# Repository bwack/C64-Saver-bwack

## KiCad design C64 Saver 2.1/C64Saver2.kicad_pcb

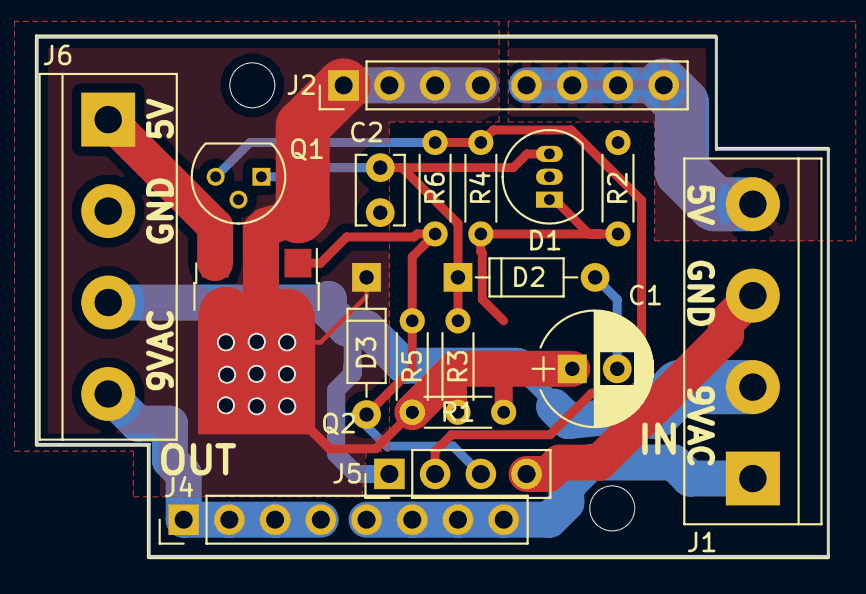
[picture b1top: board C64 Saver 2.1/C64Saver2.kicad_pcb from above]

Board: 2 copper layers, 43.9 x 28.8 mm, 20 parts (0 on the bottom side), 11 nets.

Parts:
C1: 47uF; CP_Radial_D6.3mm_P2.50mm
C2: 0.1uF; C_Disc_D3.8mm_W2.6mm_P2.50mm
D1: TL431LP; TO-92_Inline_Narrow_Oval
D2, D3: 6V8; D_DO-35_SOD27_P7.62mm_Horizontal
J1, J6: Conn_01x04; TerminalBlock_bornier-4_P5.08mm
J2, J4: Conn_01x08; Pin_Header_Straight_1x08_Pitch2.54mm
J5: Conn_01x04; Pin_Header_Straight_1x04_Pitch2.54mm
MK1, MK2: Mounting_Hole; MountingHole_2.5mm
Q1: 2N7002; TO-92_Molded_Narrow
Q2: Q_PMOS_GDS; ATPAK-2
R1, R2, R3, R4, R5, R6: R; R_Axial_DIN0204_L3.6mm_D1.6mm_P5.08mm_Horizontal

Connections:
/5V_SAFE: J6.1, Q2.3
/9VAC1: J1.1, J4.5, J4.6, J4.7, J4.8
/9VAC1': J4.1, J4.2, J4.3, J4.4, J6.4
/9VAC2: J1.2, J5.1, J6.3
/NGATE: C2.1, D1.3, D2.1, Q1.1, R3.2
/SENSE: D1.1, R1.2, R2.1, R4.1
/VCC1+: J1.4, J2.5, J2.6, J2.7, J2.8
/VCC1-: C1.1, D3.1, J2.1, J2.2, J2.3, J2.4, Q2.2, R1.1, R3.1, R5.1
GND: C1.2, C2.2, D1.2, D2.2, J1.3, J5.4, J6.2, Q1.2, R2.2
OVERVOLTAGE: J5.2, Q1.3, R4.2, R6.2
PGATE: D3.2, J5.3, Q2.1, R5.2, R6.1

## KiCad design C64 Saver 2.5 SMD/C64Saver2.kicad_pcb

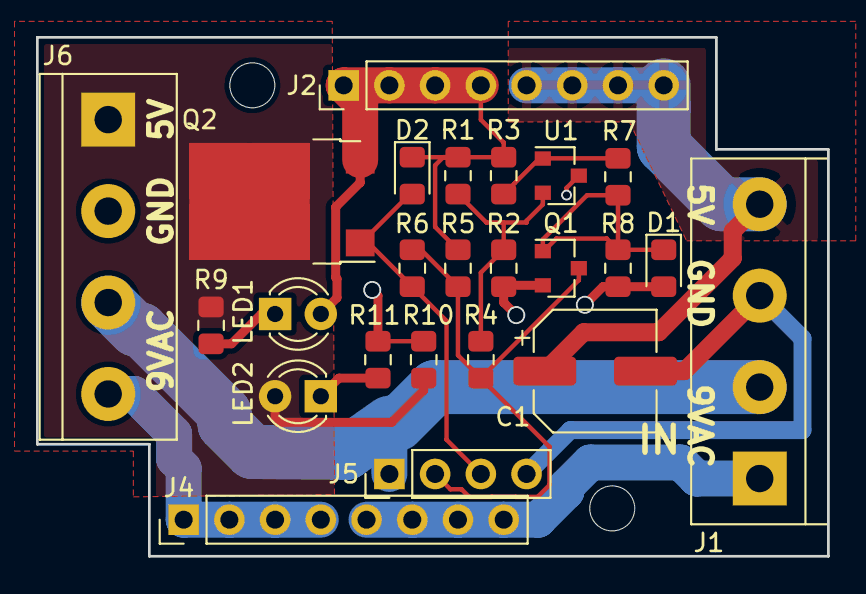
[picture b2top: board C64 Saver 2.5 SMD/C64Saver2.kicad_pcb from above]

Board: 2 copper layers, 43.9 x 28.8 mm, 26 parts (0 on the bottom side), 14 nets.

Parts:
C1: 47uF; CP_Elec_6.3x5.4
D1, D2: BZY55B6V8; D_0805_2012Metric_Pad1.15x1.40mm_HandSolder
J1, J6: Conn_01x04; TerminalBlock_bornier-4_P5.08mm
J2, J4: Conn_01x08; Pin_Header_Straight_1x08_Pitch2.54mm
J5: Conn_01x04; Pin_Header_Straight_1x04_Pitch2.54mm
LED1: LED_RED_3mm; LED_D3.0mm
LED2: LED_GREEN_3mm; LED_D3.0mm
MK1, MK2: Mounting_Hole; MountingHole_2.5mm
Q1: 2N7002; SOT-23
Q2: IRFR5305; ATPAK-2
R1, R6: 3k9; R_0805_2012Metric_Pad1.15x1.40mm_HandSolder
R2, R3, R5, R9, R10, R11: 3k3; R_0805_2012Metric_Pad1.15x1.40mm_HandSolder
R4: 330k; R_0805_2012Metric_Pad1.15x1.40mm_HandSolder
R7: 33k; R_0805_2012Metric_Pad1.15x1.40mm_HandSolder
R8: 82k; R_0805_2012Metric_Pad1.15x1.40mm_HandSolder
U1: TL431DBZ; SOT-23

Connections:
/5V_SAFE: J6.1, LED2.2, Q2.2, R9.1, R10.2
/9VAC1: J1.1, J4.5, J4.6, J4.7, J4.8
/9VAC1': J4.1, J4.2, J4.3, J4.4, J6.4
/9VAC2: J1.2, J5.1, J6.3
/NGATE: D1.1, Q1.1, R7.2, R8.1
/SENSE: R1.2, R2.1, R4.1, U1.2
/VCC1+: C1.1, J1.4, J2.5, J2.6, J2.7, J2.8
/VCC1-: D2.1, J2.1, J2.2, J2.3, J2.4, LED1.2, Q2.3, R1.1, R3.1, R5.1
GND: C1.2, D1.2, J1.3, J5.4, J6.2, Q1.2, R2.2, R8.2, R10.1, R11.1, U1.3
unnamed: LED1.1, R9.2
unnamed: LED2.1, R11.2
unnamed: R3.2, R7.1, U1.1
OVERVOLTAGE: J5.2, Q1.3, R4.2, R5.2, R6.2
PGATE: D2.2, J5.3, Q2.1, R6.1

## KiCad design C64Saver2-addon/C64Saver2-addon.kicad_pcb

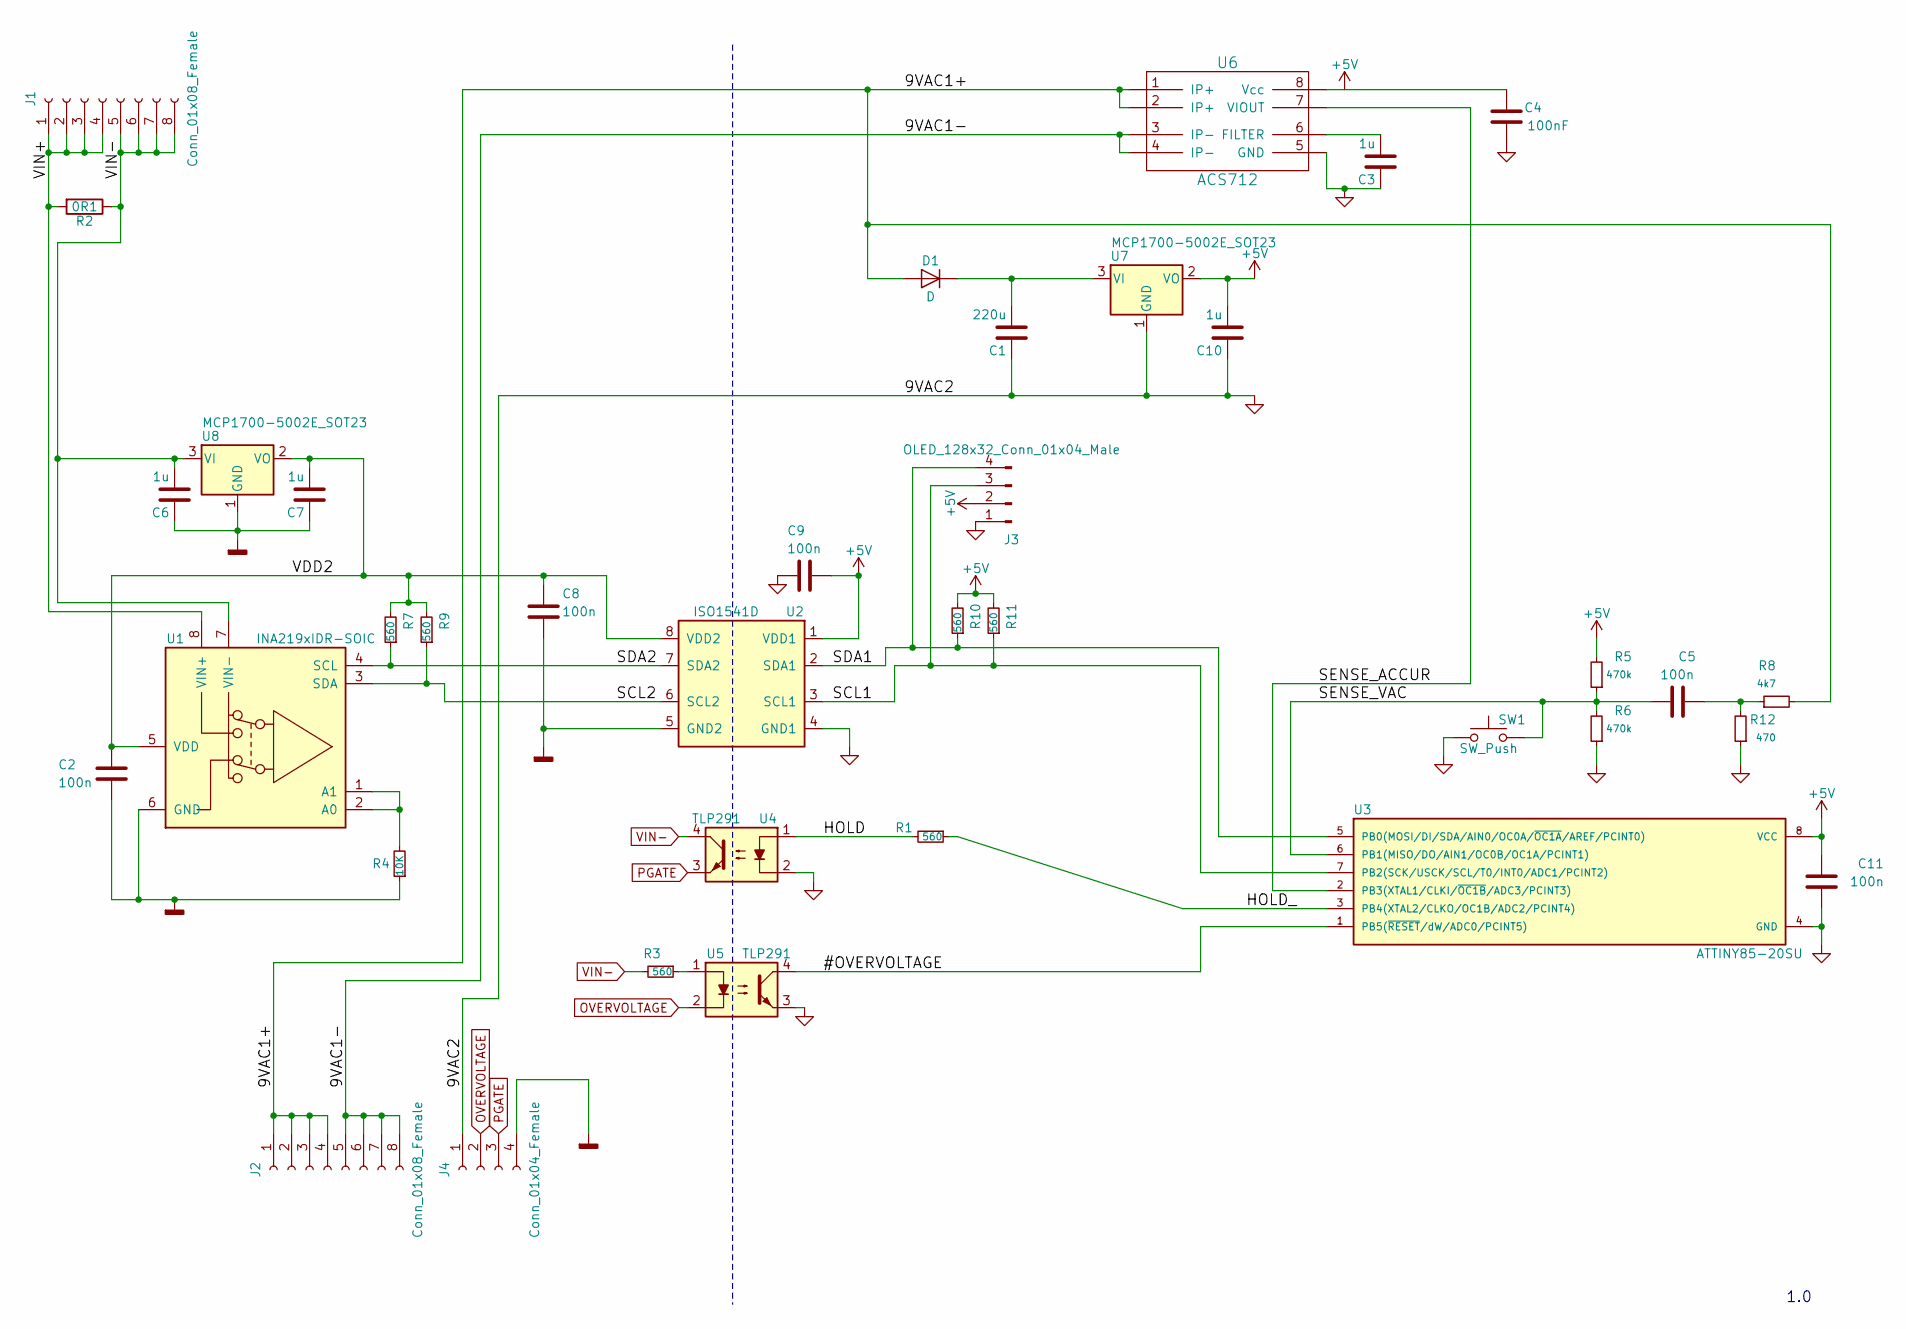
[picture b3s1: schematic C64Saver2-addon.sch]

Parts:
C1: 220u; C_1210_HandSoldering
C2, C5, C8, C9, C11: 100n; C_0603_HandSoldering
C3, C6, C7, C10: 1u; C_0603_HandSoldering
C4: 100nF; C_0603_HandSoldering
D1: D; D_SOD-123
J1, J2: Conn_01x08_Female; Pin_Header_Straight_1x08_Pitch2.54mm
J3: OLED_128x32_Conn_01x04_Male; Pin_Header_Straight_1x04_Pitch2.54mm
J4: Conn_01x04_Female; Pin_Header_Straight_1x04_Pitch2.54mm
R1, R3, R7, R9, R10, R11: 560; R_0603_HandSoldering
R2: 0R1; R_2010_HandSoldering
R4: 10K; R_0603_HandSoldering
R5, R6: 470k; R_0603_HandSoldering
R8: 4k7; R_0603_HandSoldering
R12: 470; R_0603_HandSoldering
SW1: SW_Push; SW_PUSH_6mm_h13mm
U1: INA219xIDR-SOIC; SOIC-8-N
U2: ISO1541D; SOIC-8-N
U3: ATTINY85-20SU; SOIC-8_3.9x4.9mm_Pitch1.27mm
U4, U5: TLP291; SO-4_7.6x3.6mm_Pitch2.54mm
U6: ACS712; SOIC-8-N
U7, U8: MCP1700-5002E_SOT23; SOT-23

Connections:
+5V: C4.2, C9.1, C10.2, C11.2, J3.2, R5.2, R10.2, R11.2, U2.1 (VDD1), U3.8 (VCC), U6.8 (Vcc), U7.2 (VO); also elsewhere on the board
/9VAC1+: D1.2 (A), J2.1, J2.2, J2.3, J2.4, R8.2, U6.1 (IP+), U6.2 (IP+)
/9VAC1-: J2.5, J2.6, J2.7, J2.8, U6.3 (IP-), U6.4 (IP-)
/#OVERVOLTAGE: U3.1 (PB5(~RESET~/dW/ADC0/PCINT5)), U5.4; also elsewhere on the board
/FILTER: C3.2, U6.6 (FILTER)
/HOLD: R1.2, U4.1
/HOLD_: R1.1, U3.3 (PB4(XTAL2/CLKO/OC1B/ADC2/PCINT4))
/SCL1: J3.3, R11.1, U2.3 (SCL1), U3.7 (PB2(SCK/USCK/SCL/T0/INT0/ADC1/PCINT2)); also elsewhere on the board
/SCL2: R9.1, U1.3 (SDA), U2.6 (SCL2)
/SDA1: J3.4, R10.1, U2.2 (SDA1), U3.5 (PB0(MOSI/DI/SDA/AIN0/OC0A/~OC1A~/AREF/P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); also elsewhere on the board
/SDA2: R7.1, U1.4 (SCL), U2.7 (SDA2)
/SENSE_ACCUR: U3.2 (PB3(XTAL1/CLKI/~OC1B~/ADC3/PCINT3)), U6.7 (VIOUT)
/SENSE_VAC: C5.2, R5.1, R6.2, SW1.2, U3.6 (PB1(MISO/DO/AIN1/OC0B/OC1A/PCINT1)); also elsewhere on the board
/VDD2: C2.1, C7.2, C8.1, R7.2, R9.2, U1.5 (VDD), U2.8 (VDD2), U8.2 (VO)
/VIN+: J1.1, J1.2, J1.3, J1.4, R2.2, U1.8 (VIN+)
GND: C1.1, C3.1, C4.1, C9.2, C10.1, C11.1, J3.1, J4.1, R6.1, R12.1, SW1.1, U2.4 (GND1), U3.4 (GND), U4.2, U5.3, U6.5 (GND), U7.1 (GND); also elsewhere on the board
GNDD: C2.2, C6.1, C7.1, C8.2, J4.4, R4.1, U1.6 (GND), U2.5 (GND2), U8.1 (GND)
unnamed: C1.2, D1.1 (K), U7.3 (VI)
unnamed: C5.1, R8.1, R12.2
unnamed: R3.1, U5.1
unnamed: R4.2, U1.1 (A1), U1.2 (A0)
OVERVOLTAGE: J4.2, U5.2
PGATE: J4.3, U4.3
VIN-: C6.2, J1.5, J1.6, J1.7, J1.8, R2.1, R3.2, U1.7 (VIN-), U4.4, U8.3 (VI)

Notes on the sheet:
1.0

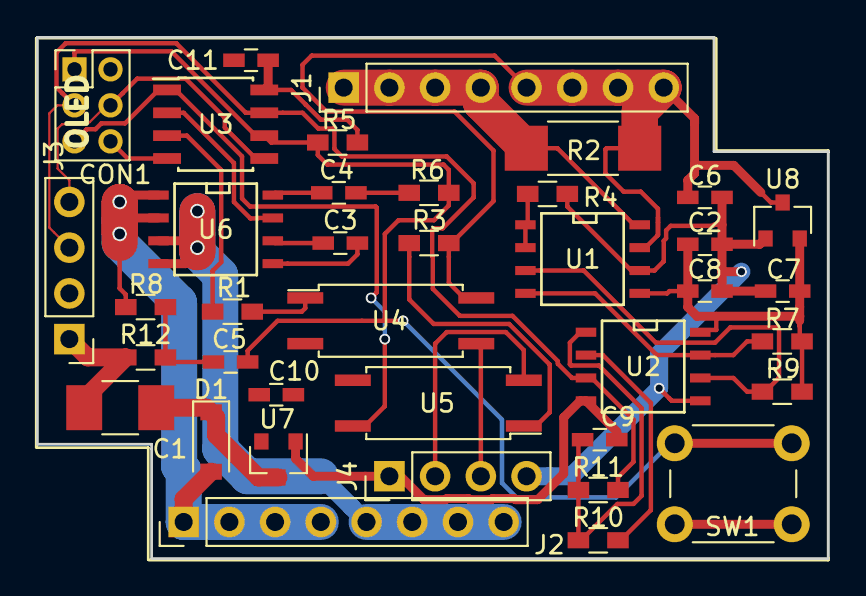
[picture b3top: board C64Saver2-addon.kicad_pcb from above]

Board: 2 copper layers, 43.9 x 29.0 mm, 38 parts (0 on the bottom side), 24 nets.

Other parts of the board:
CON1: AVR-ISP-6; Pin_Header_Straight_2x03_Pitch2.00mm

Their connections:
+5V: CON1.2; also elsewhere on the board
/#OVERVOLTAGE: CON1.5; also elsewhere on the board
/SCL1: CON1.3; also elsewhere on the board
/SDA1: CON1.4; also elsewhere on the board
/SENSE_VAC: CON1.1; also elsewhere on the board
GND: CON1.6; also elsewhere on the board

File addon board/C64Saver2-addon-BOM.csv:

"Source:","D:\Documents\GitHub\C64-Saver-bwack\addon board\C64Saver2-addon.sch"
"Date:","24.05.2019 00:26:36"
"Tool:","Eeschema (5.1.0)-1"
"Generator:","C:\Program Files\KiCad\bin\scripting\plugins/bom_csv_grouped_by_value.py"
"Component Count:","42"

"Individual Components:"

"Item","Qty","Reference(s)","Value","LibPart","Footprint","Datasheet"
"","","C1","47uF","Device:C_Small","Capacitor_SMD:C_1206_3216Metric","~"
"","","C2","100n","Device:C","Capacitors_SMD:C_0603_HandSoldering",""
"","","C3","1u","Device:C","Capacitors_SMD:C_0603_HandSoldering",""
"","","C4","100nF","Device:C","Capacitors_SMD:C_0603_HandSoldering",""
"","","C5","100n","Device:C","Capacitors_SMD:C_0603_HandSoldering",""
"","","C6","1u","Device:C","Capacitors_SMD:C_0603_HandSoldering",""
"","","C7","1u","Device:C","Capacitors_SMD:C_0603_HandSoldering",""
"","","C8","100n","Device:C","Capacitors_SMD:C_0603_HandSoldering",""
"","","C9","100n","Device:C","Capacitors_SMD:C_0603_HandSoldering",""
"","","C10","1u","Device:C","Capacitors_SMD:C_0603_HandSoldering",""
"","","C11","100n","Device:C","Capacitors_SMD:C_0603_HandSoldering",""
"","","C12","47uF","Device:C_Small","Capacitor_SMD:C_1206_3216Metric","~"
"","","C13","47uF","Device:C_Small","Capacitor_SMD:C_1206_3216Metric","~"
"","","CON1","AVR-ISP-6","C64Saver2-addon-rescue:AVR-ISP-6","Pin_Headers:Pin_Header_Straight_2x03_Pitch2.00mm",""
"","","D1","Dotec SL1G","Device:D","Diodes_SMD:D_SOD-123",""
"","","J1","Conn_01x08_Female","C64Saver2-addon-rescue:Conn_01x08_Female","Pin_Headers:Pin_Header_Straight_1x08_Pitch2.54mm",""
"","","J2","Conn_01x08_Female","C64Saver2-addon-rescue:Conn_01x08_Female","Pin_Headers:Pin_Header_Straight_1x08_Pitch2.54mm",""
"","","J3","OLED_128x32_Conn_01x04_Male","C64Saver2-addon-rescue:Conn_01x04_Male","Pin_Headers:Pin_Header_Straight_1x04_Pitch2.54mm",""
"","","J4","Conn_01x04_Female","C64Saver2-addon-rescue:Conn_01x04_Female","Pin_Headers:Pin_Header_Straight_1x04_Pitch2.54mm",""
"","","R1","560","Device:R_Small","Resistors_SMD:R_0603_HandSoldering",""
"","","R2","0R1","Device:R","Resistors_SMD:R_2512_HandSoldering",""
"","","R3","560","Device:R_Small","Resistors_SMD:R_0603_HandSoldering",""
"","","R4","10K","Device:R_Small","Resistors_SMD:R_0603_HandSoldering",""
"","","R5","470k","Device:R_Small","Resistors_SMD:R_0603_HandSoldering",""
"","","R6","470k","Device:R_Small","Resistors_SMD:R_0603_HandSoldering",""
"","","R7","4k7","Device:R_Small","Resistors_SMD:R_0603_HandSoldering",""
"","","R8","4k7","Device:R_Small","Resistors_SMD:R_0603_HandSoldering",""
"","","R9","4k7","Device:R_Small","Resistors_SMD:R_0603_HandSoldering",""
"","","R10","4k7","Device:R_Small","Resistors_SMD:R_0603_HandSoldering",""
"","","R11","4k7","Device:R_Small","Resistors_SMD:R_0603_HandSoldering",""
"","","R12","470","Device:R_Small","Resistors_SMD:R_0603_HandSoldering",""
"","","R13","10k","Device:R_Small","Resistors_SMD:R_0603_HandSoldering",""
"","","R14","1k","Device:R_Small","Resistors_SMD:R_0603_HandSoldering",""
"","","SW1","SW_Push","C64Saver2-addon-rescue:SW_Push","Buttons_Switches_THT:SW_PUSH_6mm_h13mm",""
"","","U1","INA219xIDR-SOIC","ina219:INA219xIDR-SOIC","SMD_Packages:SOIC-8-N",""
"","","U2","ISO1541D","iso1541d:ISO1541D","SMD_Packages:SOIC-8-N",""
"","","U3","ATTINY85-20SU","C64Saver2-addon-rescue:ATTINY85-20SU","Housings_SOIC:SOIJ-8_5.3x5.3mm_Pitch1.27mm",""
"","","U4","ACPL-217-50DE","C64Saver2-addon-rescue:TLP291","Package_SO:SOIC-4_4.55x2.6mm_P1.27mm",""
"","","U5","ACPL-217-50DE","C64Saver2-addon-rescue:TLP291","Package_SO:SOIC-4_4.55x2.6mm_P1.27mm",""
"","","U6","ACS712","acs712:ACS712","SMD_Packages:SOIC-8-N",""
"","","U7","MCP1703","C64Saver2-addon-rescue:MCP1700-5002E_SOT23","Package_TO_SOT_SMD:SOT-223-3_TabPin2",""
"","","U8","MCP1703","C64Saver2-addon-rescue:MCP1700-5002E_SOT23","TO_SOT_Packages_SMD:SOT-23",""



"Collated Components:"

"Item","Qty","Reference(s)","Value","LibPart","Footprint","Datasheet"
"1","3","C1, C12, C13","47uF","Device:C_Small","Capacitor_SMD:C_1206_3216Metric","~"
"2","5","C2, C5, C8, C9, C11","100n","Device:C","Capacitors_SMD:C_0603_HandSoldering",""
"3","4","C3, C6, C7, C10","1u","Device:C","Capacitors_SMD:C_0603_HandSoldering",""
"4","1","C4","100nF","Device:C","Capacitors_SMD:C_0603_HandSoldering",""
"5","1","CON1","AVR-ISP-6","C64Saver2-addon-rescue:AVR-ISP-6","Pin_Headers:Pin_Header_Straight_2x03_Pitch2.00mm",""
"6","1","D1","Dotec SL1G","Device:D","Diodes_SMD:D_SOD-123",""
"7","2","J1, J2","Conn_01x08_Female","C64Saver2-addon-rescue:Conn_01x08_Female","Pin_Headers:Pin_Header_Straight_1x08_Pitch2.54mm",""
"8","1","J3","OLED_128x32_Conn_01x04_Male","C64Saver2-addon-rescue:Conn_01x04_Male","Pin_Headers:Pin_Header_Straight_1x04_Pitch2.54mm",""
"9","1","J4","Conn_01x04_Female","C64Saver2-addon-rescue:Conn_01x04_Female","Pin_Headers:Pin_Header_Straight_1x04_Pitch2.54mm",""
"10","2","R1, R3","560","Device:R_Small","Resistors_SMD:R_0603_HandSoldering",""
"11","1","R2","0R1","Device:R","Resistors_SMD:R_2512_HandSoldering",""
"12","1","R4","10K","Device:R_Small","Resistors_SMD:R_0603_HandSoldering",""
"13","2","R5, R6","470k","Device:R_Small","Resistors_SMD:R_0603_HandSoldering",""
"14","5","R7, R8, R9, R10, R11","4k7","Device:R_Small","Resistors_SMD:R_0603_HandSoldering",""
"15","1","R12","470","Device:R_Small","Resistors_SMD:R_0603_HandSoldering",""
"16","1","R13","10k","Device:R_Small","Resistors_SMD:R_0603_HandSoldering",""
"17","1","R14","1k","Device:R_Small","Resistors_SMD:R_0603_HandSoldering",""
"18","1","SW1","SW_Push","C64Saver2-addon-rescue:SW_Push","Buttons_Switches_THT:SW_PUSH_6mm_h13mm",""
"19","1","U1","INA219xIDR-SOIC","ina219:INA219xIDR-SOIC","SMD_Packages:SOIC-8-N",""
"20","1","U2","ISO1541D","iso1541d:ISO1541D","SMD_Packages:SOIC-8-N",""
"21","1","U3","ATTINY85-20SU","C64Saver2-addon-rescue:ATTINY85-20SU","Housings_SOIC:SOIJ-8_5.3x5.3mm_Pitch1.27mm",""
"22","2","U4, U5","ACPL-217-50DE","C64Saver2-addon-rescue:TLP291","Package_SO:SOIC-4_4.55x2.6mm_P1.27mm",""
"23","1","U6","ACS712","acs712:ACS712","SMD_Packages:SOIC-8-N",""
"24","1","U7","MCP1703","C64Saver2-addon-rescue:MCP1700-5002E_SOT23","Package_TO_SOT_SMD:SOT-223-3_TabPin2",""
"25","1","U8","MCP1703","C64Saver2-addon-rescue:MCP1700-5002E_SOT23","TO_SOT_Packages_SMD:SOT-23",""

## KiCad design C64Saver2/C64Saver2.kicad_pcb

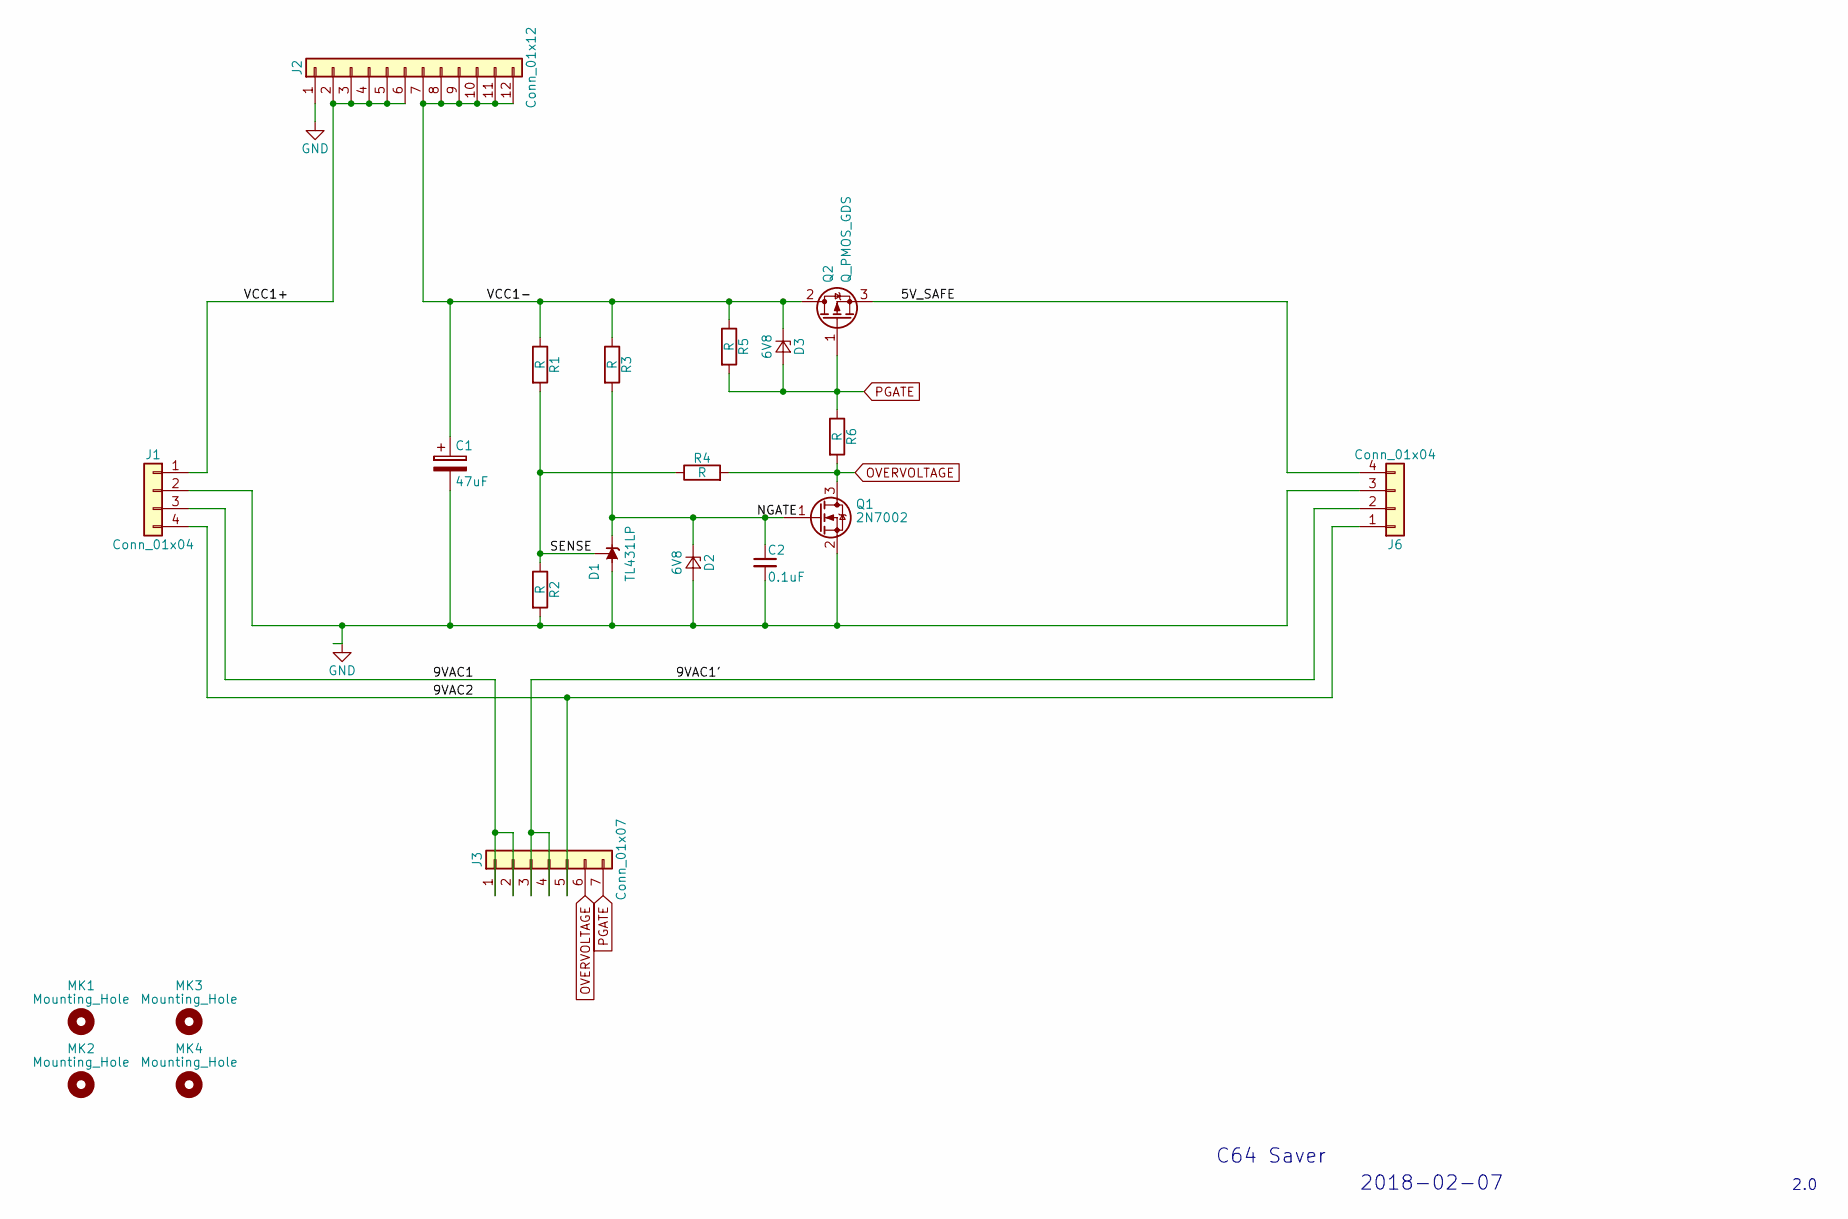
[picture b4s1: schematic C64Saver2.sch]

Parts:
C1: 47uF; CP_Radial_D6.3mm_P2.50mm
C2: 0.1uF; C_Disc_D3.8mm_W2.6mm_P2.50mm
D1: TL431LP; TO-92_Inline_Narrow_Oval
D2, D3: 6V8; D_DO-35_SOD27_P7.62mm_Horizontal
J1, J6: Conn_01x04; TerminalBlock_bornier-4_P5.08mm
J2: Conn_01x12; Pin_Header_Straight_1x12_Pitch2.54mm
J3: Conn_01x07; Pin_Header_Straight_1x07_Pitch2.54mm
MK1, MK2, MK3, MK4: Mounting_Hole; MountingHole_3.2mm_M3_ISO7380
Q1: 2N7002; TO-92_Molded_Narrow
Q2: Q_PMOS_GDS; ATPAK-2
R1, R2, R3, R4, R5, R6: R; R_Axial_DIN0207_L6.3mm_D2.5mm_P10.16mm_Horizontal

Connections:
/5V_SAFE: J6.4, Q2.3 (S)
/9VAC1: J1.3, J3.1, J3.2
/9VAC1': J3.3, J3.4, J6.2
/9VAC2: J1.4, J3.5, J6.1
/NGATE: C2.1, D1.3 (K), D2.1 (K), Q1.1 (G), R3.2
/SENSE: D1.1 (REF), R1.2, R2.1, R4.1
/VCC1+: J1.1, J2.2, J2.3, J2.4, J2.5, J2.6
/VCC1-: C1.1, D3.1 (K), J2.7, J2.8, J2.9, J2.10, J2.11, J2.12, Q2.2 (D), R1.1, R3.1, R5.1
GND: C1.2, C2.2, D1.2 (A), D2.2 (A), J1.2, J2.1, J6.3, Q1.2 (S), R2.2
OVERVOLTAGE: J3.6, Q1.3 (D), R4.2, R6.2
PGATE: D3.2 (A), J3.7, Q2.1 (G), R5.2, R6.1

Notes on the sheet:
2.0
C64 Saver
2018-02-07

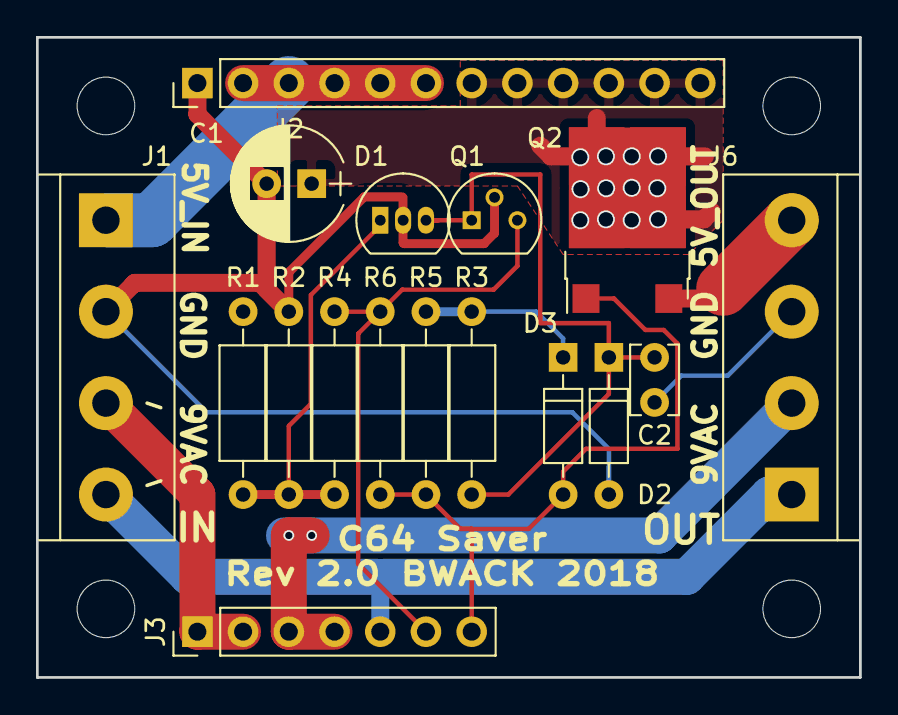
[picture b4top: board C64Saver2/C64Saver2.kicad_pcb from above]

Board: 2 copper layers, 45.7 x 35.6 mm, 21 parts (0 on the bottom side), 11 nets.
